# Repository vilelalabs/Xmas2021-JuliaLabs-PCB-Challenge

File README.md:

# Xmas2021-JuliaLabs-PCB-Challenge

## Descrição Geral
Esta placa foi desenvolvida para o concurso "Julialabs PCB Challenge" de 2021 com um tema natalino.
A idéia geral foi fazer um enfeite de para a árvore de natal (a estrela que normalmente é colocada no topo da árvore) que funcione de maneira automática (ao inserir a bateria) fazendo sequências "pisca-pisca" nas pontas principais da mesma (inclusive há buracos na parte interior da placa para se passar uma fita ou linha para afixar a placa na árvore de natal!)
### Funcionamento
Para funcionar ela só precisará de uma bateria 3V tipo CR1220 (facilmente encontrada - a famosa "bateria de relógio") para iniciar automaticamente a apresentação de uma sequências de acendimento de LEDs predefinidos (por software) que destacam os oito cantos principais da estrela.
As sequências (não necessarimanete nesta ordem) são:
-  Alternando os 4 cantos internos (LEDs azuis) e os 4 cantos externos (LEDs brancos)
- Fazendo uma volta completa  piscando no sentido horário e anti-horário
- Piscando todos os Leds acesos e apagados entre estas sequências.

### Hardware
O Hardware foi desenvolvido usando o software [Eagle](https://github.com/vilelalabs/Xmas2021-JuliaLabs-PCB-Challenge/tree/master/HARDWARE/eagle), incluindo aqui:
- O esquemático
- A placa de circuito impresso
- O arquivo gerber para fabricação. 

Já a simulação do funcionamento do circuito foi realizada utilizando o software [Proteus](https://github.com/vilelalabs/Xmas2021-JuliaLabs-PCB-Challenge/tree/master/HARDWARE/proteus).

**_Todos os arquivos referentes ao desenvolvimento do Hardware se encontram na pasta [HARDWARE](https://github.com/vilelalabs/Xmas2021-JuliaLabs-PCB-Challenge/tree/master/HARDWARE)_**

### Software / Firmware
- O software foi desenvolvido em C++ usando a extensão PlatformIO para a IDE VSCode. Nele temos macros (#define) para cada led individualmente e para grupos dos leds (por cor, ou considerandos todos os leds simultaneamente). O código principal pode ser encontrado na pasta [SRC](https://github.com/vilelalabs/Xmas2021-JuliaLabs-PCB-Challenge/tree/master/SOFTWARE/src).
- O código no arquivo **_main.cpp_** também pode ser utilizado normalmente na Arduino IDE, desde que realizadas as devidas configurações para a correta programação do Attiny85 na mesma.

**_Todos arquivos referentes ao desenvolvimento do software no PlatformIO estão na pasta [SOFTWARE](https://github.com/vilelalabs/Xmas2021-JuliaLabs-PCB-Challenge/tree/master/SOFTWARE)_**

### Observações
- Foram usados encapsulamentos SOIC e componentes SMD de solda manual fácil para uma experiência fácil também na montagem.
- Os LEDs devem ser colocados lateralmente (virados para as mesmas direções) ou, se possível, com uma orientação para o lado interno da placa (que poderia ser possível com um "ajuste" na hora da soldagem) aproveitando melhor as partes translúcidas da placa.
- Todo o processo foi transmitido em stream na [Twitch](https://twitch.tv/vilelalabs) e parte desse desenvolvimento será destacado no [Youtube](https://youtube.com/vilelalabs) futuramente.
- Toda parte "verde" da placa deveria ser "azul" **a ser escolhido no momento da fabricação**. Infelizmente nao consegui fazer este setup no Eagle ou nas visualizações do projeto.

### Imagens
|Placa|Esquemático|
|:----------:|:----------:|
|   |  |
|Visualização 3D|Simulação|
|   |  |

### Lista de Componentes
|Componente|Quantidade|Observação| Datasheet|
|:----------:|:----------:|:----------:|:----------:|
| [ATTINY85V-10SNR](https://br.mouser.com/ProductDetail/556-ATTINY25V-10SNR)  | 1  | Microcontrolador  | [Datasheet](https://br.mouser.com/datasheet/2/268/Atmel-2586-AVR-8-bit-Microcontroller-ATtiny25-ATti-1315542.pdf)|
| [SN74HC595D](https://br.mouser.com/ProductDetail/595-SN74HC595DRE4)  | 1  | Registrador de deslocamento de 8 bits  | [Datasheet](https://www.ti.com/lit/ds/symlink/sn74hc595.pdf?HQS=dis-mous-null-mousermode-dsf-pf-null-wwe&ts=1641509615811&ref_url=https%253A%252F%252Fwww.mouser.be%252F)|
| [Clip de Bateria CR1220](https://br.mouser.com/ProductDetail/534-3000TR)  | 1  | Modelo Keystone 3000TR | [Datasheet](https://br.mouser.com/datasheet/2/215/3000TR-742873.pdf)|
| [Resistor 150Ω](https://br.mouser.com/ProductDetail/71-TNPW0805150RFEEA)  | 8  | Observacao  | [Datasheet](https://br.mouser.com/datasheet/2/427/tnpw_e3-1761965.pdf)|
| [LED Branco](https://br.mouser.com/ProductDetail/720-LWA67CS2U25K8LZ)  | 4  | montagem lateral / SMD  |[Datasheet](https://dammedia.osram.info/media/resource/hires/osram-dam-6455804/LW%20A67C%20binning%20FK0PN0_EN.pdf)|
| [LED Azul](https://br.mouser.com/ProductDetail/859-LTST-S220TBKT)  | 4  | montagem lateral / SMD  |[Datasheet](https://br.mouser.com/datasheet/2/239/Lite-On-LTST-S220TBKT-1175488.pdf)|

### Links
- [Carrinho de compras na Mouser](https://br.mouser.com/ProjectManager/ProjectDetail.aspx?AccessID=1f4f7a85bd)
- [Projeto na PCBWay](https://www.pcbway.com/project/shareproject/Blinking_Christmas_Star_e158be5a.html)

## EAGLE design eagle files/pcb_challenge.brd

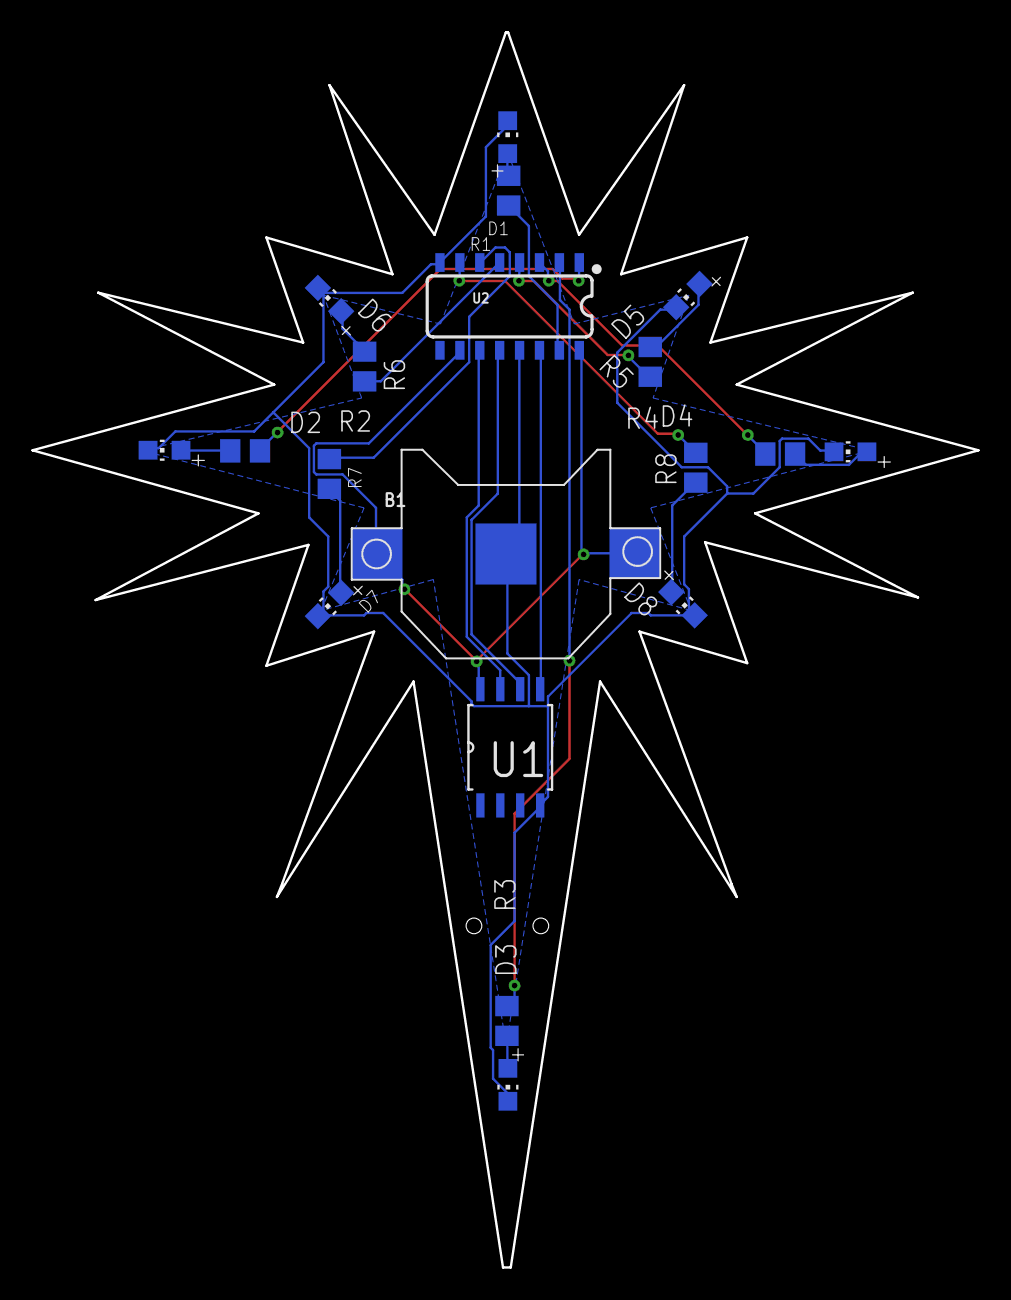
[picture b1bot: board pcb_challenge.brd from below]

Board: 2 copper layers, 60.4 x 78.8 mm, 19 parts (19 on the bottom side), 21 nets.

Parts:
B1: CR1220; CR1220-SMD
D1, D2, D3, D4: WLED; CHIP-LED0805
D5, D6, D7, D8: BLED; CHIP-LED0805
R1, R2, R3, R4, R5, R6, R7, R8: 150; R0805
U1: ATTINY85V-10SU; SOIC127P798X216-8N
U2: SN74HC595D; SO16

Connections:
CLOCK: U1.7, U2.11
DATA: U1.5, U2.14
GND: B1.-, D1.C, D2.C, D3.C, D4.C, D5.C, D6.C, D7.C, D8.C, U1.4, U2.8, U2.13
LATCH: U1.6, U2.12
unnamed: D5.A, R5.1
unnamed: D4.A, R4.1
unnamed: D3.A, R3.1
unnamed: D2.A, R2.1
unnamed: D1.A, R1.1
unnamed: D8.A, R8.1
unnamed: D7.A, R7.1
unnamed: D6.A, R6.1
unnamed: R1.2, U2.15
unnamed: R2.2, U2.1
unnamed: R3.2, U2.2
unnamed: R4.2, U2.3
unnamed: R5.2, U2.4
unnamed: R8.2, U2.7
unnamed: R7.2, U2.6
unnamed: R6.2, U2.5
VCC: B1.+$1, B1.+$2, U1.8, U2.10, U2.16

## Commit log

2022-01-07 Upload eagle files
2022-01-07 Update README.md
    Tradução para português, adição de campos e formatação.
2022-01-07 uploaded the bmp files that the project was based
2022-01-07 Adicionado imagens e BOM
2022-01-07 added gerber file
2022-01-07 new folders
2022-01-07 added hardware section
2022-01-07 Hardware description updated

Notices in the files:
parts and their libraries:
SparkFun-IC-Logic: Licensing: Creative Commons ShareAlike 4.0 International - https://creativecommons.org/licenses/by-sa/4.0
